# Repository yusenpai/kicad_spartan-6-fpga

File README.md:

# Spartan 6 FPGA Dev Board

Đây là thiết kế của một board FPGA dựa trên Xilinx Spartan-6 XC6SLX16, kiểu chân BGA 324 chân. Board tương thích với slot mini PCI Express. Trên board tích hợp 256MB DRAM DDR3, 1Gb NAND Flash và 32Mb NOR Flash phục vụ cho mục đích lưu trữ file cấu hình FPGA.
Board này phục vụ cho mục đích học tập, nghiên cứu liên quan tới FPGA.

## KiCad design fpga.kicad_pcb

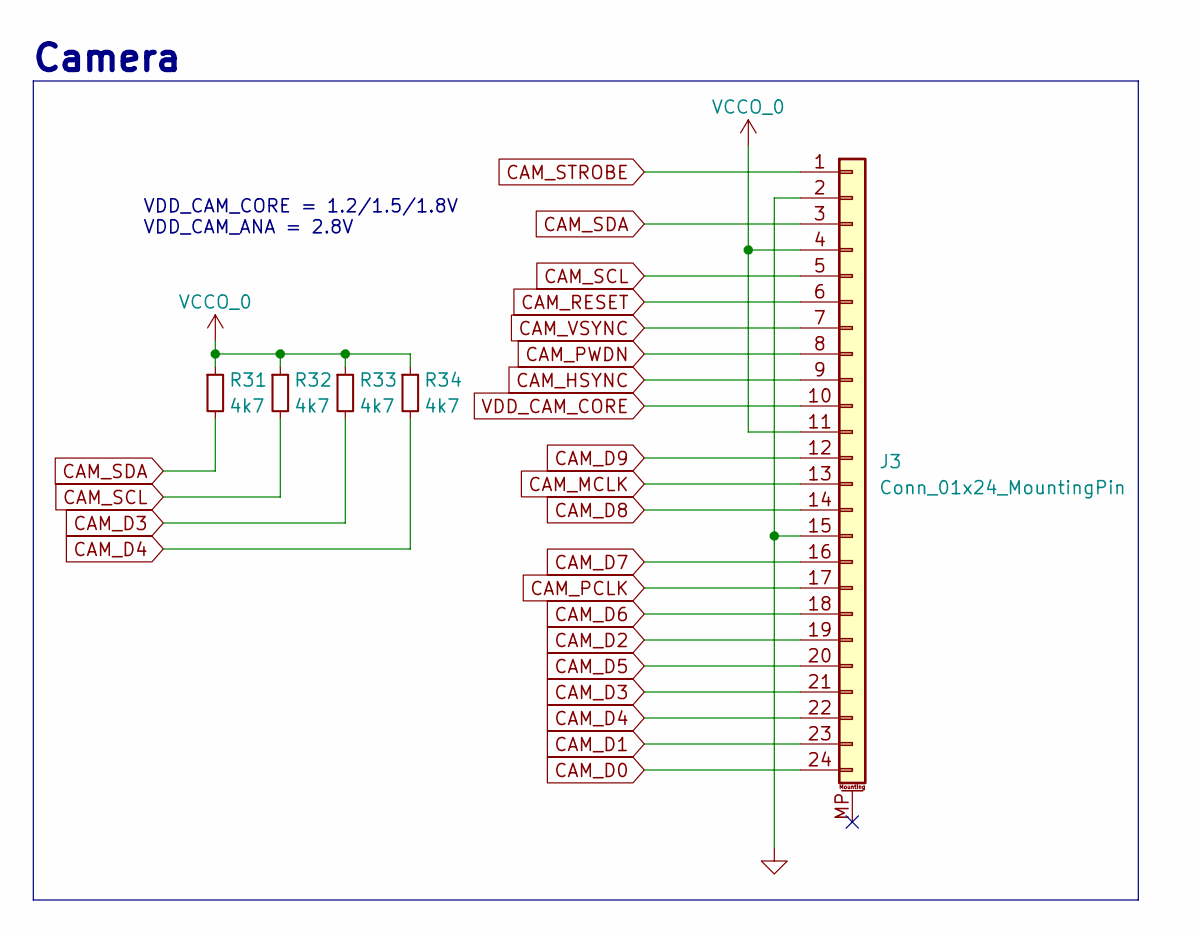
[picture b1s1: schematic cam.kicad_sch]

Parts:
J3: Conn_01x24_MountingPin; FPC-24P0.5
R31, R32, R33, R34: 4k7; R_0402_1005Metric

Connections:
+3V3: J3.4, J3.11, R31.1, R32.1, R33.1, R34.1; also elsewhere on the board
CAM_D0: J3.24; also elsewhere on the board
CAM_D1: J3.23; also elsewhere on the board
CAM_D2: J3.19; also elsewhere on the board
CAM_D3: J3.21, R33.2; also elsewhere on the board
CAM_D4: J3.22, R34.2; also elsewhere on the board
CAM_D5: J3.20; also elsewhere on the board
CAM_D6: J3.18; also elsewhere on the board
CAM_D7: J3.16; also elsewhere on the board
CAM_D8: J3.14; also elsewhere on the board
CAM_D9: J3.12; also elsewhere on the board
CAM_HSYNC: J3.9; also elsewhere on the board
CAM_MCLK: J3.13; also elsewhere on the board
CAM_PCLK: J3.17; also elsewhere on the board
CAM_PWDN: J3.8; also elsewhere on the board
CAM_RESET: J3.6; also elsewhere on the board
CAM_SCL: J3.5, R32.2; also elsewhere on the board
CAM_SDA: J3.3, R31.2; also elsewhere on the board
CAM_STROBE: J3.1; also elsewhere on the board
CAM_VSYNC: J3.7; also elsewhere on the board
GND: J3.2, J3.15; also elsewhere on the board
VDD_CAM_CORE: J3.10; also elsewhere on the board

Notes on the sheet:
Camera
VDD_CAM_CORE = 1.2/1.5/1.8V VDD_CAM_ANA = 2.8V

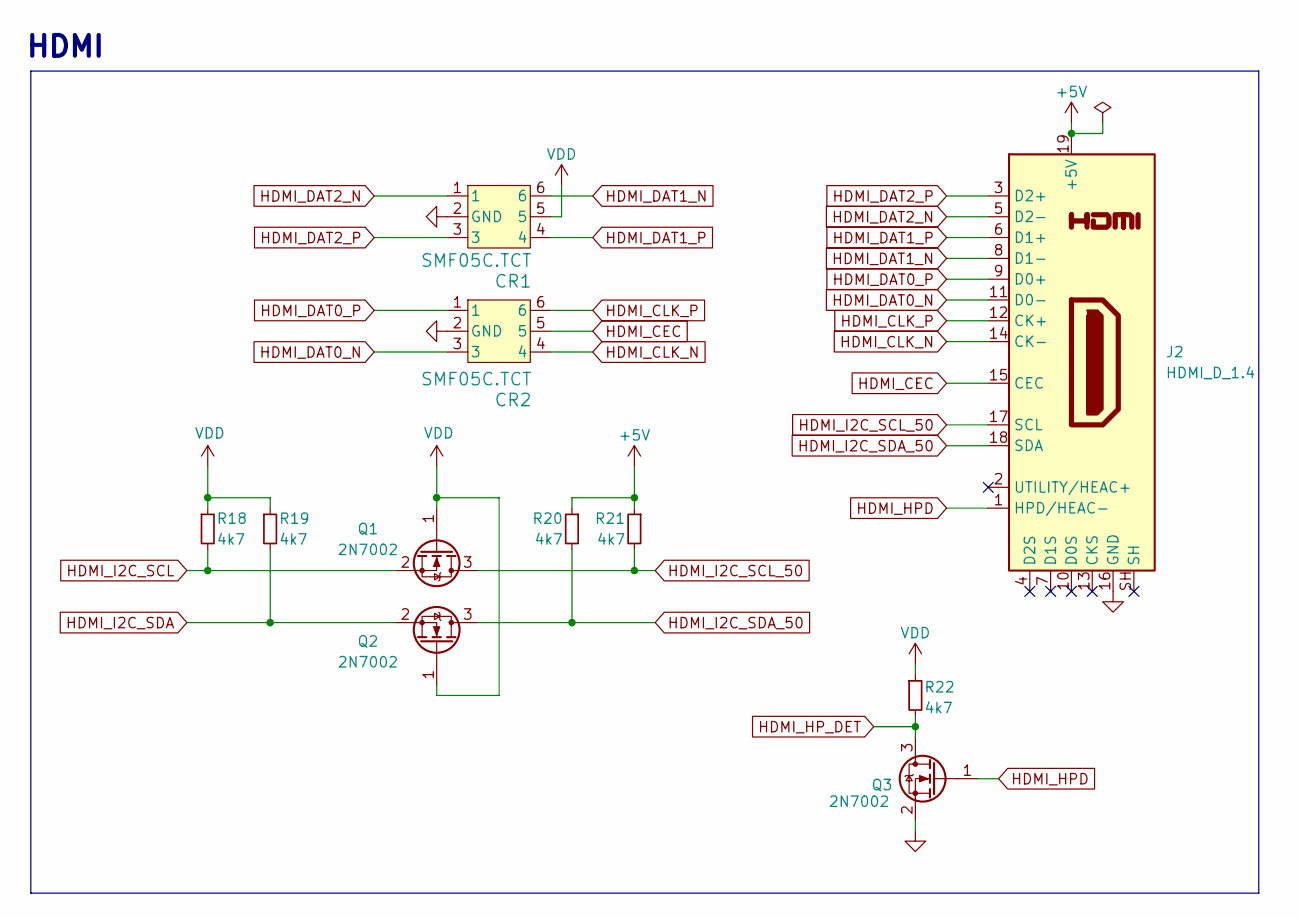
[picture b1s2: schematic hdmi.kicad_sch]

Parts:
CR1, CR2: SMF05C.TCT; TSOT-23-6
J2: HDMI_D_1.4; HDMI_Micro-D_Molex_46765-0x01
Q1, Q2, Q3: 2N7002; SOT-23
R18, R19, R20, R21, R22: 4k7; R_0402_1005Metric

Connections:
+3V3: CR1.5, Q1.1 (G), Q2.1 (G), R18.1, R19.1, R22.1; also elsewhere on the board
+5V: J2.19 (+5V), R20.1, R21.1; also elsewhere on the board
GND: CR1.2 (GND), CR2.2 (GND), J2.16 (GND), Q3.2 (S); also elsewhere on the board
HDMI_CEC: CR2.5, J2.15 (CEC); also elsewhere on the board
HDMI_CLK_N: CR2.4, J2.14 (CK-); also elsewhere on the board
HDMI_CLK_P: CR2.6, J2.12 (CK+); also elsewhere on the board
HDMI_DAT0_N: CR2.3, J2.11 (D0-); also elsewhere on the board
HDMI_DAT0_P: CR2.1, J2.9 (D0+); also elsewhere on the board
HDMI_DAT1_N: CR1.6, J2.8 (D1-); also elsewhere on the board
HDMI_DAT1_P: CR1.4, J2.6 (D1+); also elsewhere on the board
HDMI_DAT2_N: CR1.1, J2.5 (D2-); also elsewhere on the board
HDMI_DAT2_P: CR1.3, J2.3 (D2+); also elsewhere on the board
HDMI_HPD: J2.1 (HPD/HEAC-), Q3.1 (G)
HDMI_HP_DET: Q3.3 (D), R22.2; also elsewhere on the board
HDMI_I2C_SCL: Q1.2 (S), R18.2; also elsewhere on the board
HDMI_I2C_SCL_50: J2.17 (SCL), Q1.3 (D), R21.2
HDMI_I2C_SDA: Q2.2 (S), R19.2; also elsewhere on the board
HDMI_I2C_SDA_50: J2.18 (SDA), Q2.3 (D), R20.2

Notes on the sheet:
HDMI

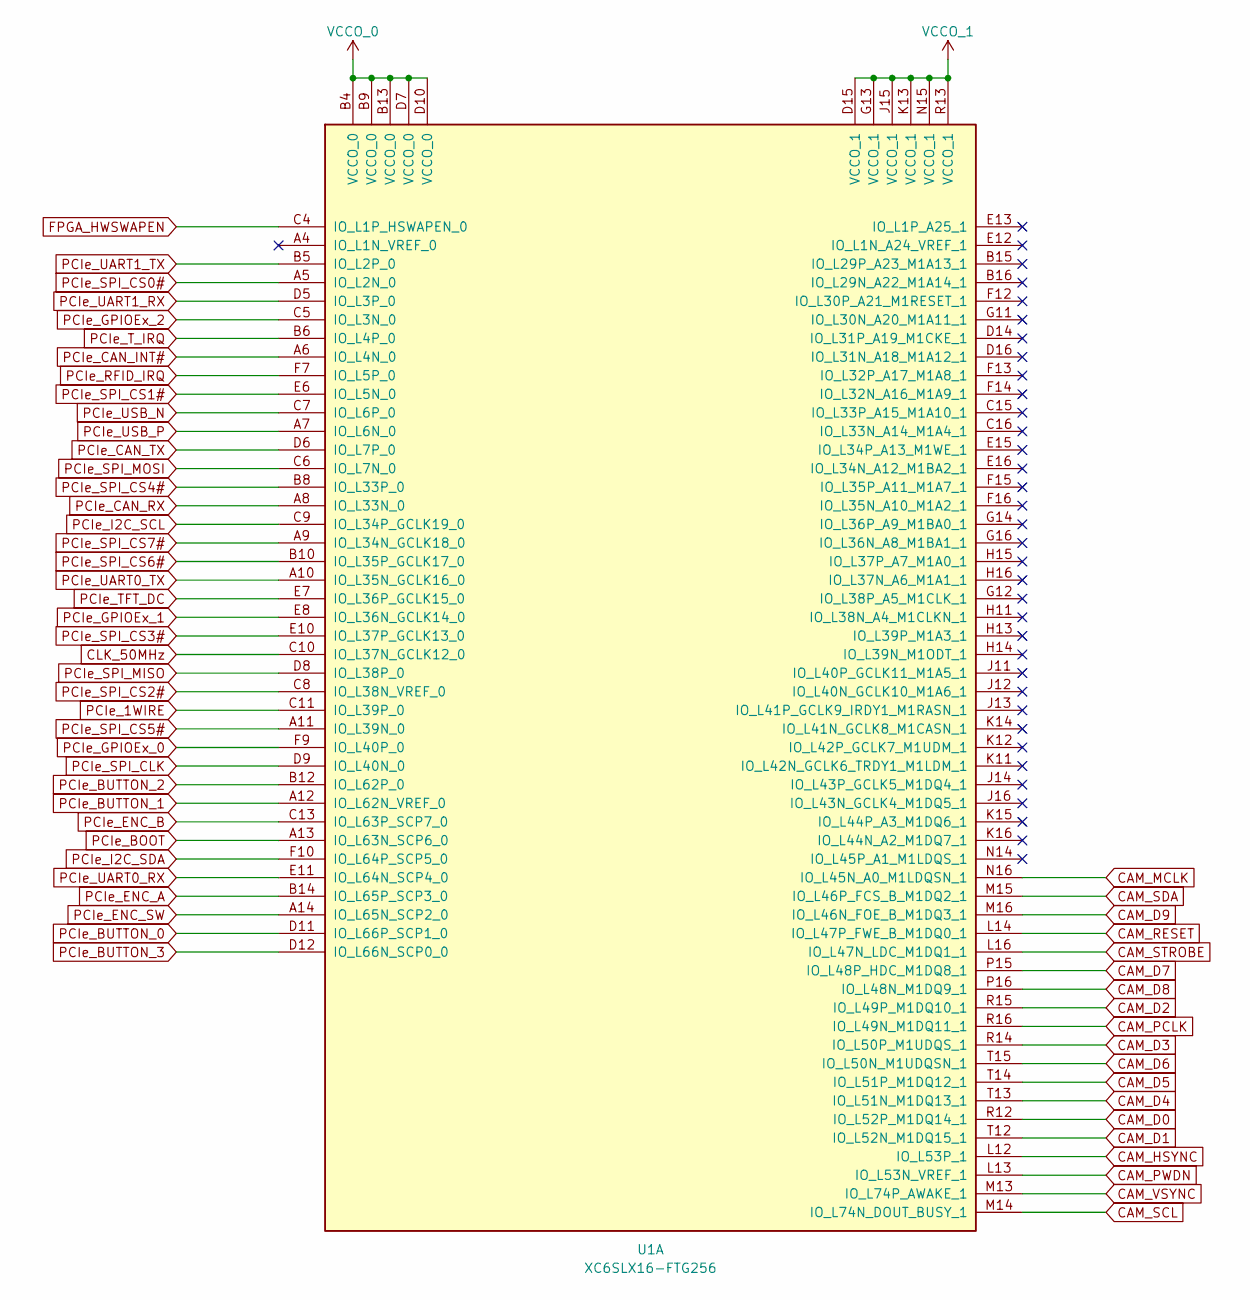
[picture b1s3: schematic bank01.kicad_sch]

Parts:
U1: XC6SLX16-FTG256; BGA-256_17.0x17.0mm_Layout16x16_P1.0mm_Ball0.5mm_Pad0.4mm_N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

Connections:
+2V8: U1.D15 (VCCO_1), U1.G13 (VCCO_1), U1.J15 (VCCO_1), U1.K13 (VCCO_1), U1.N15 (VCCO_1), U1.R13 (VCCO_1); also elsewhere on the board
+3V3: U1.B4 (VCCO_0), U1.B9 (VCCO_0), U1.B13 (VCCO_0), U1.D7 (VCCO_0), U1.D10 (VCCO_0); also elsewhere on the board
CAM_D0: U1.R12 (IO_L52P_M1DQ14_1); also elsewhere on the board
CAM_D1: U1.T12 (IO_L52N_M1DQ15_1); also elsewhere on the board
CAM_D2: U1.R15 (IO_L49P_M1DQ10_1); also elsewhere on the board
CAM_D3: U1.R14 (IO_L50P_M1UDQS_1); also elsewhere on the board
CAM_D4: U1.T13 (IO_L51N_M1DQ13_1); also elsewhere on the board
CAM_D5: U1.T14 (IO_L51P_M1DQ12_1); also elsewhere on the board
CAM_D6: U1.T15 (IO_L50N_M1UDQSN_1); also elsewhere on the board
CAM_D7: U1.P15 (IO_L48P_HDC_M1DQ8_1); also elsewhere on the board
CAM_D8: U1.P16 (IO_L48N_M1DQ9_1); also elsewhere on the board
CAM_D9: U1.M16 (IO_L46N_FOE_B_M1DQ3_1); also elsewhere on the board
CAM_HSYNC: U1.L12 (IO_L53P_1); also elsewhere on the board
CAM_MCLK: U1.N16 (IO_L45N_A0_M1LDQSN_1); also elsewhere on the board
CAM_PCLK: U1.R16 (IO_L49N_M1DQ11_1); also elsewhere on the board
CAM_PWDN: U1.L13 (IO_L53N_VREF_1); also elsewhere on the board
CAM_RESET: U1.L14 (IO_L47P_FWE_B_M1DQ0_1); also elsewhere on the board
CAM_SCL: U1.M14 (IO_L74N_DOUT_BUSY_1); also elsewhere on the board
CAM_SDA: U1.M15 (IO_L46P_FCS_B_M1DQ2_1); also elsewhere on the board
CAM_STROBE: U1.L16 (IO_L47N_LDC_M1DQ1_1); also elsewhere on the board
CAM_VSYNC: U1.M13 (IO_L74P_AWAKE_1); also elsewhere on the board
CLK_50MHz: U1.C10 (IO_L37N_GCLK12_0); also elsewhere on the board
FPGA_HWSWAPEN: U1.C4 (IO_L1P_HSWAPEN_0); also elsewhere on the board
PCIe_1WIRE: U1.C11 (IO_L39P_0); also elsewhere on the board
PCIe_BOOT: U1.A13 (IO_L63N_SCP6_0); also elsewhere on the board
PCIe_BUTTON_0: U1.D11 (IO_L66P_SCP1_0); also elsewhere on the board
PCIe_BUTTON_1: U1.A12 (IO_L62N_VREF_0); also elsewhere on the board
PCIe_BUTTON_2: U1.B12 (IO_L62P_0); also elsewhere on the board
PCIe_BUTTON_3: U1.D12 (IO_L66N_SCP0_0); also elsewhere on the board
PCIe_CAN_INT#: U1.A6 (IO_L4N_0); also elsewhere on the board
PCIe_CAN_RX: U1.A8 (IO_L33N_0); also elsewhere on the board
PCIe_CAN_TX: U1.D6 (IO_L7P_0); also elsewhere on the board
PCIe_ENC_A: U1.B14 (IO_L65P_SCP3_0); also elsewhere on the board
PCIe_ENC_B: U1.C13 (IO_L63P_SCP7_0); also elsewhere on the board
PCIe_ENC_SW: U1.A14 (IO_L65N_SCP2_0); also elsewhere on the board
PCIe_GPIOEx_0: U1.F9 (IO_L40P_0); also elsewhere on the board
PCIe_GPIOEx_1: U1.E8 (IO_L36N_GCLK14_0); also elsewhere on the board
PCIe_GPIOEx_2: U1.C5 (IO_L3N_0); also elsewhere on the board
PCIe_I2C_SCL: U1.C9 (IO_L34P_GCLK19_0); also elsewhere on the board
PCIe_I2C_SDA: U1.F10 (IO_L64P_SCP5_0); also elsewhere on the board
PCIe_RFID_IRQ: U1.F7 (IO_L5P_0); also elsewhere on the board
PCIe_SPI_CLK: U1.D9 (IO_L40N_0); also elsewhere on the board
PCIe_SPI_CS0#: U1.A5 (IO_L2N_0); also elsewhere on the board
PCIe_SPI_CS1#: U1.E6 (IO_L5N_0); also elsewhere on the board
PCIe_SPI_CS2#: U1.C8 (IO_L38N_VREF_0); also elsewhere on the board
PCIe_SPI_CS3#: U1.E10 (IO_L37P_GCLK13_0); also elsewhere on the board
PCIe_SPI_CS4#: U1.B8 (IO_L33P_0); also elsewhere on the board
PCIe_SPI_CS5#: U1.A11 (IO_L39N_0); also elsewhere on the board
PCIe_SPI_CS6#: U1.B10 (IO_L35P_GCLK17_0); also elsewhere on the board
PCIe_SPI_CS7#: U1.A9 (IO_L34N_GCLK18_0); also elsewhere on the board
PCIe_SPI_MISO: U1.D8 (IO_L38P_0); also elsewhere on the board
PCIe_SPI_MOSI: U1.C6 (IO_L7N_0); also elsewhere on the board
PCIe_TFT_DC: U1.E7 (IO_L36P_GCLK15_0); also elsewhere on the board
PCIe_T_IRQ: U1.B6 (IO_L4P_0); also elsewhere on the board
PCIe_UART0_RX: U1.E11 (IO_L64N_SCP4_0); also elsewhere on the board
PCIe_UART0_TX: U1.A10 (IO_L35N_GCLK16_0); also elsewhere on the board
PCIe_UART1_RX: U1.D5 (IO_L3P_0); also elsewhere on the board
PCIe_UART1_TX: U1.B5 (IO_L2P_0); also elsewhere on the board
PCIe_USB_N: U1.C7 (IO_L6P_0); also elsewhere on the board
PCIe_USB_P: U1.A7 (IO_L6N_0); also elsewhere on the board

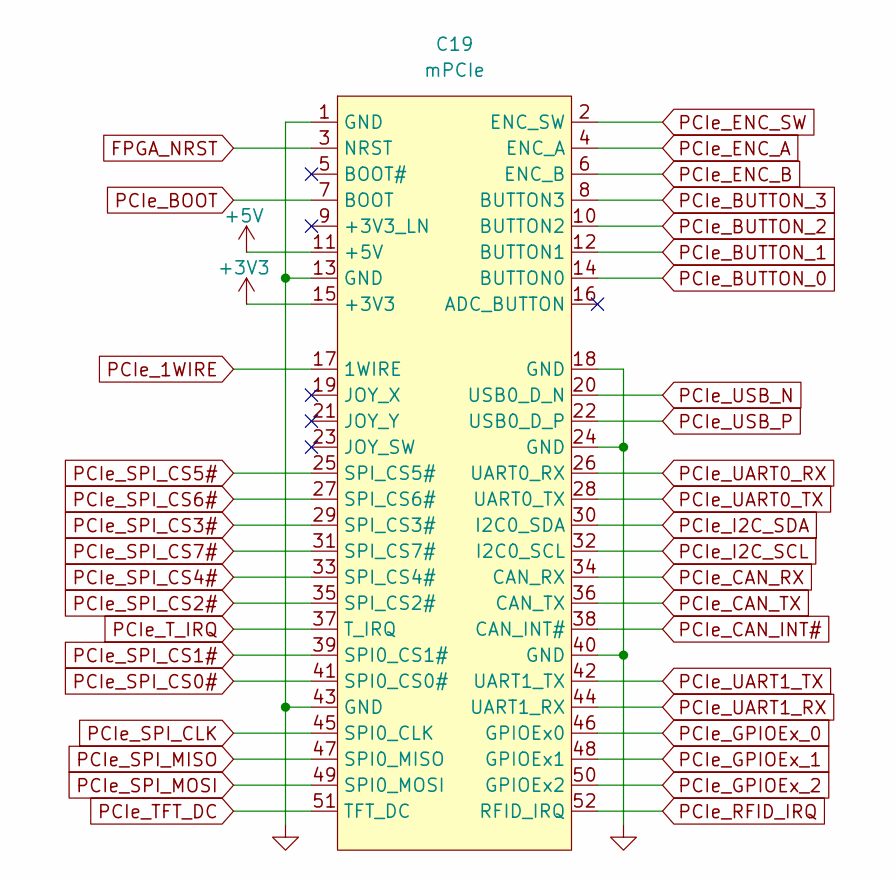
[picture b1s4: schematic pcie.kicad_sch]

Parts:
C19: mPCIe; mpcie-full-card

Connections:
+3V3: C19.15 (+3V3); also elsewhere on the board
+5V: C19.11 (+5V); also elsewhere on the board
FPGA_NRST: C19.3 (NRST); also elsewhere on the board
GND: C19.1 (GND), C19.13 (GND), C19.18 (GND), C19.24 (GND), C19.40 (GND), C19.43 (GND); also elsewhere on the board
PCIe_1WIRE: C19.17 (1WIRE); also elsewhere on the board
PCIe_BOOT: C19.7 (BOOT); also elsewhere on the board
PCIe_BUTTON_0: C19.14 (BUTTON0); also elsewhere on the board
PCIe_BUTTON_1: C19.12 (BUTTON1); also elsewhere on the board
PCIe_BUTTON_2: C19.10 (BUTTON2); also elsewhere on the board
PCIe_BUTTON_3: C19.8 (BUTTON3); also elsewhere on the board
PCIe_CAN_INT#: C19.38 (CAN_INT#); also elsewhere on the board
PCIe_CAN_RX: C19.34 (CAN_RX); also elsewhere on the board
PCIe_CAN_TX: C19.36 (CAN_TX); also elsewhere on the board
PCIe_ENC_A: C19.4 (ENC_A); also elsewhere on the board
PCIe_ENC_B: C19.6 (ENC_B); also elsewhere on the board
PCIe_ENC_SW: C19.2 (ENC_SW); also elsewhere on the board
PCIe_GPIOEx_0: C19.46 (GPIOEx0); also elsewhere on the board
PCIe_GPIOEx_1: C19.48 (GPIOEx1); also elsewhere on the board
PCIe_GPIOEx_2: C19.50 (GPIOEx2); also elsewhere on the board
PCIe_I2C_SCL: C19.32 (I2C0_SCL); also elsewhere on the board
PCIe_I2C_SDA: C19.30 (I2C0_SDA); also elsewhere on the board
PCIe_RFID_IRQ: C19.52 (RFID_IRQ); also elsewhere on the board
PCIe_SPI_CLK: C19.45 (SPI0_CLK); also elsewhere on the board
PCIe_SPI_CS0#: C19.41 (SPI0_CS0#); also elsewhere on the board
PCIe_SPI_CS1#: C19.39 (SPI0_CS1#); also elsewhere on the board
PCIe_SPI_CS2#: C19.35 (SPI_CS2#); also elsewhere on the board
PCIe_SPI_CS3#: C19.29 (SPI_CS3#); also elsewhere on the board
PCIe_SPI_CS4#: C19.33 (SPI_CS4#); also elsewhere on the board
PCIe_SPI_CS5#: C19.25 (SPI_CS5#); also elsewhere on the board
PCIe_SPI_CS6#: C19.27 (SPI_CS6#); also elsewhere on the board
PCIe_SPI_CS7#: C19.31 (SPI_CS7#); also elsewhere on the board
PCIe_SPI_MISO: C19.47 (SPI0_MISO); also elsewhere on the board
PCIe_SPI_MOSI: C19.49 (SPI0_MOSI); also elsewhere on the board
PCIe_TFT_DC: C19.51 (TFT_DC); also elsewhere on the board
PCIe_T_IRQ: C19.37 (T_IRQ); also elsewhere on the board
PCIe_UART0_RX: C19.26 (UART0_RX); also elsewhere on the board
PCIe_UART0_TX: C19.28 (UART0_TX); also elsewhere on the board
PCIe_UART1_RX: C19.44 (UART1_RX); also elsewhere on the board
PCIe_UART1_TX: C19.42 (UART1_TX); also elsewhere on the board
PCIe_USB_N: C19.20 (USB0_D_N); also elsewhere on the board
PCIe_USB_P: C19.22 (USB0_D_P); also elsewhere on the board

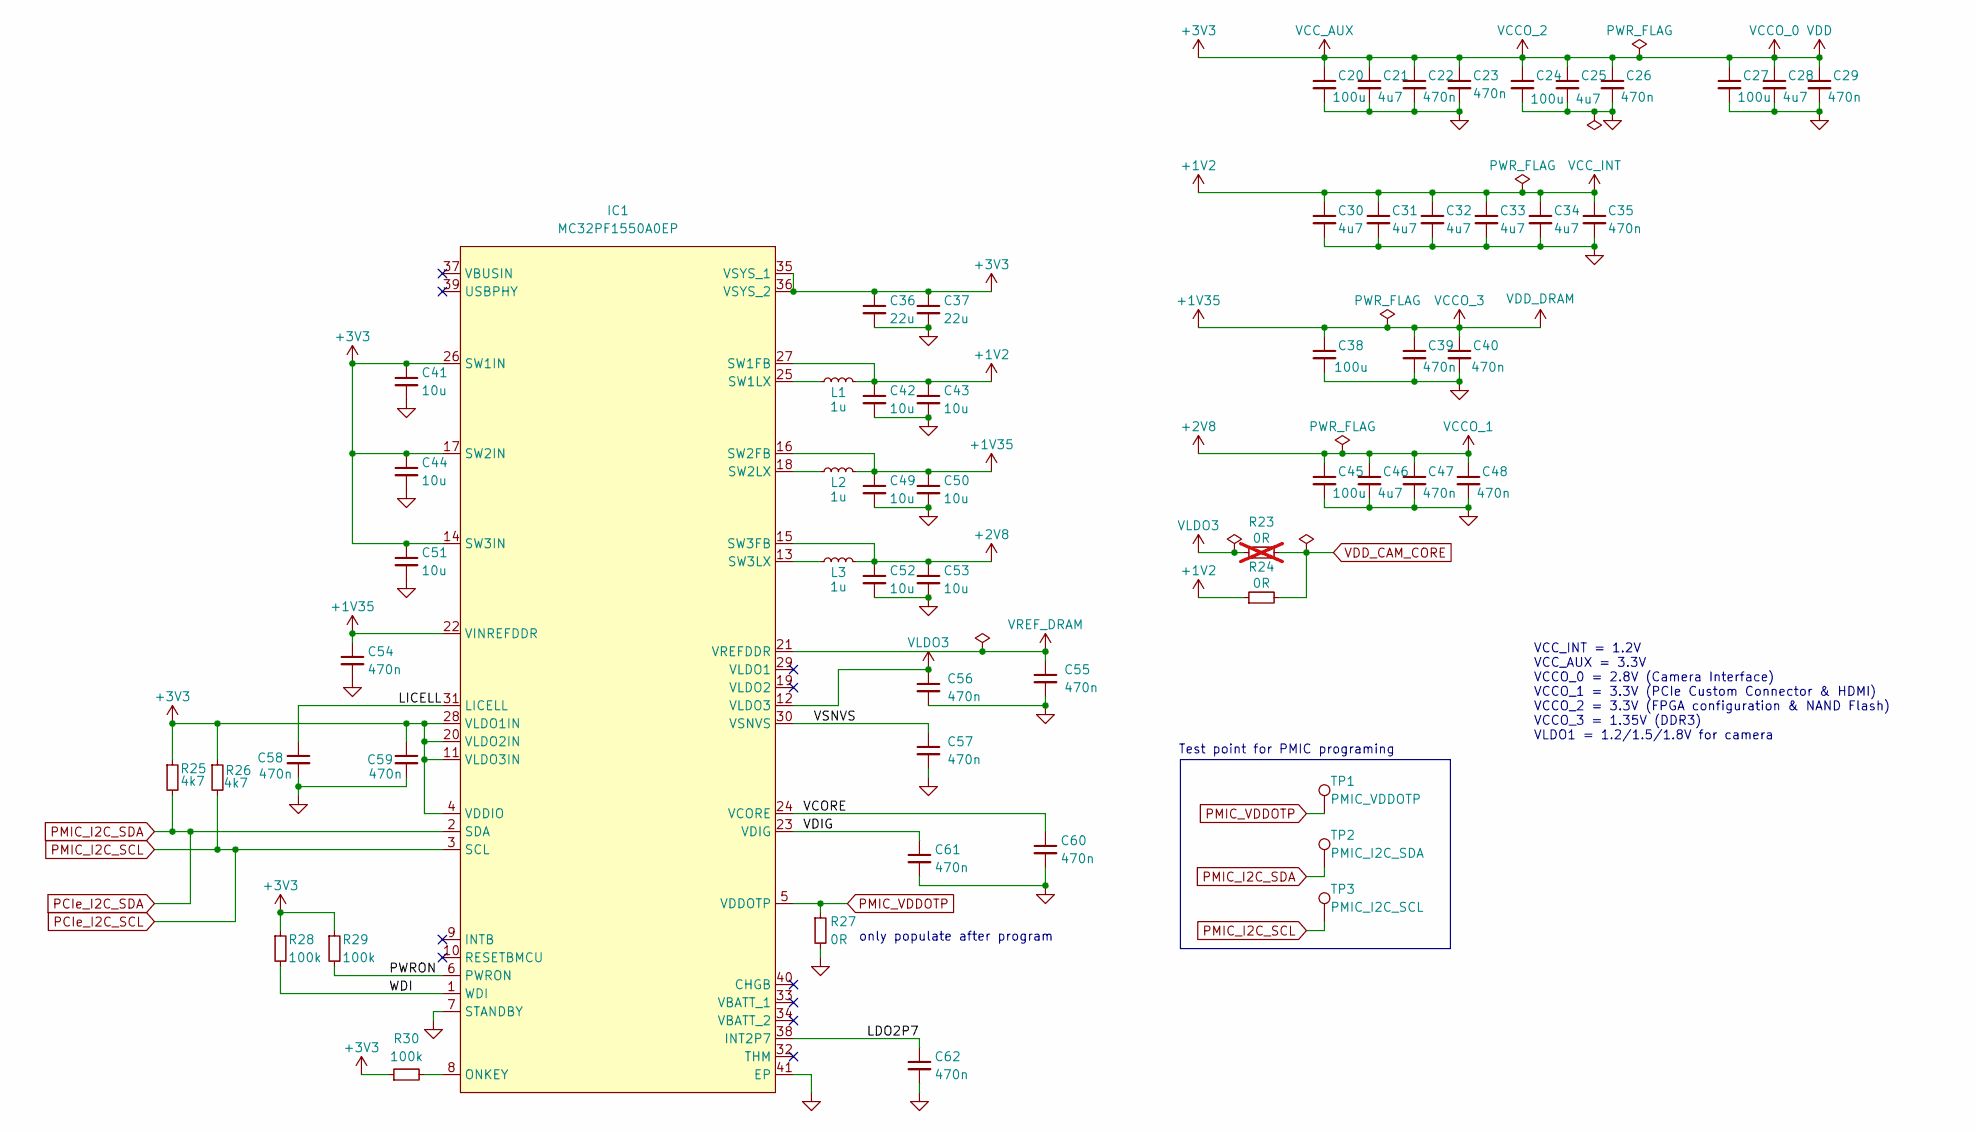
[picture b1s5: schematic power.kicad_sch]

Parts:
C20, C24, C27, C38, C45: 100u; C_1206_3216Metric
C21, C25, C28, C30, C31, C32, C33, C34, C46: 4u7; C_0603_1608Metric
C22, C23, C26, C29, C35, C39, C40, C47, C48, C54, C55, C56, C57, C58, C59, C60, C61, C62: 470n; C_0402_1005Metric
C36, C37: 22u; C_0603_1608Metric
C41, C42, C43, C44, C49, C50, C51, C52, C53: 10u; C_0603_1608Metric
IC1: MC32PF1550A0EP; QFN-40-1EP_5x5mm_P0.4mm_EP3.8x3.8mm; Manufacturer_Part_Number MC32PF1550A0EP; Mouser Part Number 771-MC32PF1550A0EP
L1, L2, L3: 1u; L_Wurth_WE-LQSH-4020
R23: 0R; R_0402_1005Metric; not fitted
R24, R27: 0R; R_0402_1005Metric
R25, R26: 4k7; R_0402_1005Metric
R28, R29, R30: 100k; R_0402_1005Metric
TP1: PMIC_VDDOTP; TestPoint_Pad_D1.0mm
TP2: PMIC_I2C_SDA; TestPoint_Pad_D1.0mm
TP3: PMIC_I2C_SCL; TestPoint_Pad_D1.0mm

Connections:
+1V2: C30.1, C31.1, C32.1, C33.1, C34.1, C35.1, C42.1, C43.1, IC1.27 (SW1FB), L1.2, R24.1; also elsewhere on the board
+1V35: C38.1, C39.1, C40.1, C49.1, C50.1, C54.1, IC1.16 (SW2FB), IC1.22 (VINREFDDR), L2.2; also elsewhere on the board
+2V8: C45.1, C46.1, C47.1, C48.1, C52.1, C53.1, IC1.15 (SW3FB), L3.2; also elsewhere on the board
+3V3: C20.1, C21.1, C22.1, C23.1, C24.1, C25.1, C26.1, C27.1, C28.1, C29.1, C36.1, C37.1, C41.1, C44.1, C51.1, C59.1, IC1.4 (VDDIO), IC1.11 (VLDO3IN), IC1.14 (SW3IN), IC1.17 (SW2IN), IC1.20 (VLDO2IN), IC1.26 (SW1IN), IC1.28 (VLDO1IN), IC1.35 (VSYS_1), IC1.36 (VSYS_2), R25.1, R26.1, R28.1, R29.1, R30.1; also elsewhere on the board
/Power/LDO2P7: C62.1, IC1.38 (INT2P7)
/Power/LICELL: C58.1, IC1.31 (LICELL)
/Power/PWRON: IC1.6 (PWRON), R29.2
/Power/VCORE: C60.1, IC1.24 (VCORE)
/Power/VDIG: C61.1, IC1.23 (VDIG)
/Power/VSNVS: C57.1, IC1.30 (VSNVS)
/Power/WDI: IC1.1 (WDI), R28.2
GND: C20.2, C21.2, C22.2, C23.2, C24.2, C25.2, C26.2, C27.2, C28.2, C29.2, C30.2, C31.2, C32.2, C33.2, C34.2, C35.2, C36.2, C37.2, C38.2, C39.2, C40.2, C41.2, C42.2, C43.2, C44.2, C45.2, C46.2, C47.2, C48.2, C49.2, C50.2, C51.2, C52.2, C53.2, C54.2, C55.2, C56.2, C57.2, C58.2, C59.2, C60.2, C61.2, C62.2, IC1.7 (STANDBY), IC1.41 (EP), R27.2; also elsewhere on the board
unnamed: IC1.8 (ONKEY), R30.2
unnamed: IC1.25 (SW1LX), L1.1
unnamed: IC1.18 (SW2LX), L2.1
unnamed: IC1.13 (SW3LX), L3.1
PCIe_I2C_SCL: IC1.3 (SCL), R26.2, TP3.1; also elsewhere on the board
PCIe_I2C_SDA: IC1.2 (SDA), R25.2, TP2.1; also elsewhere on the board
PMIC_VDDOTP: IC1.5 (VDDOTP), R27.1, TP1.1
VDD_CAM_CORE: R23.2, R24.2; also elsewhere on the board
VLDO3: C56.1, IC1.12 (VLDO3), R23.1
VREF_DRAM: C55.1, IC1.21 (VREFDDR); also elsewhere on the board

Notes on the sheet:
only populate after program
VCC_INT = 1.2V VCC_AUX = 3.3V VCCO_0 = 2.8V (Camera Interface) VCCO_1 = 3.3V (PCIe Custom Connector & HDMI) VCCO_2 = 3.3V (FPGA configuration & NAND Flash) VCCO_3 = 1.35V (DDR3) VLDO1 = 1.2/1.5/1.8V for camera
Test point for PMIC programing

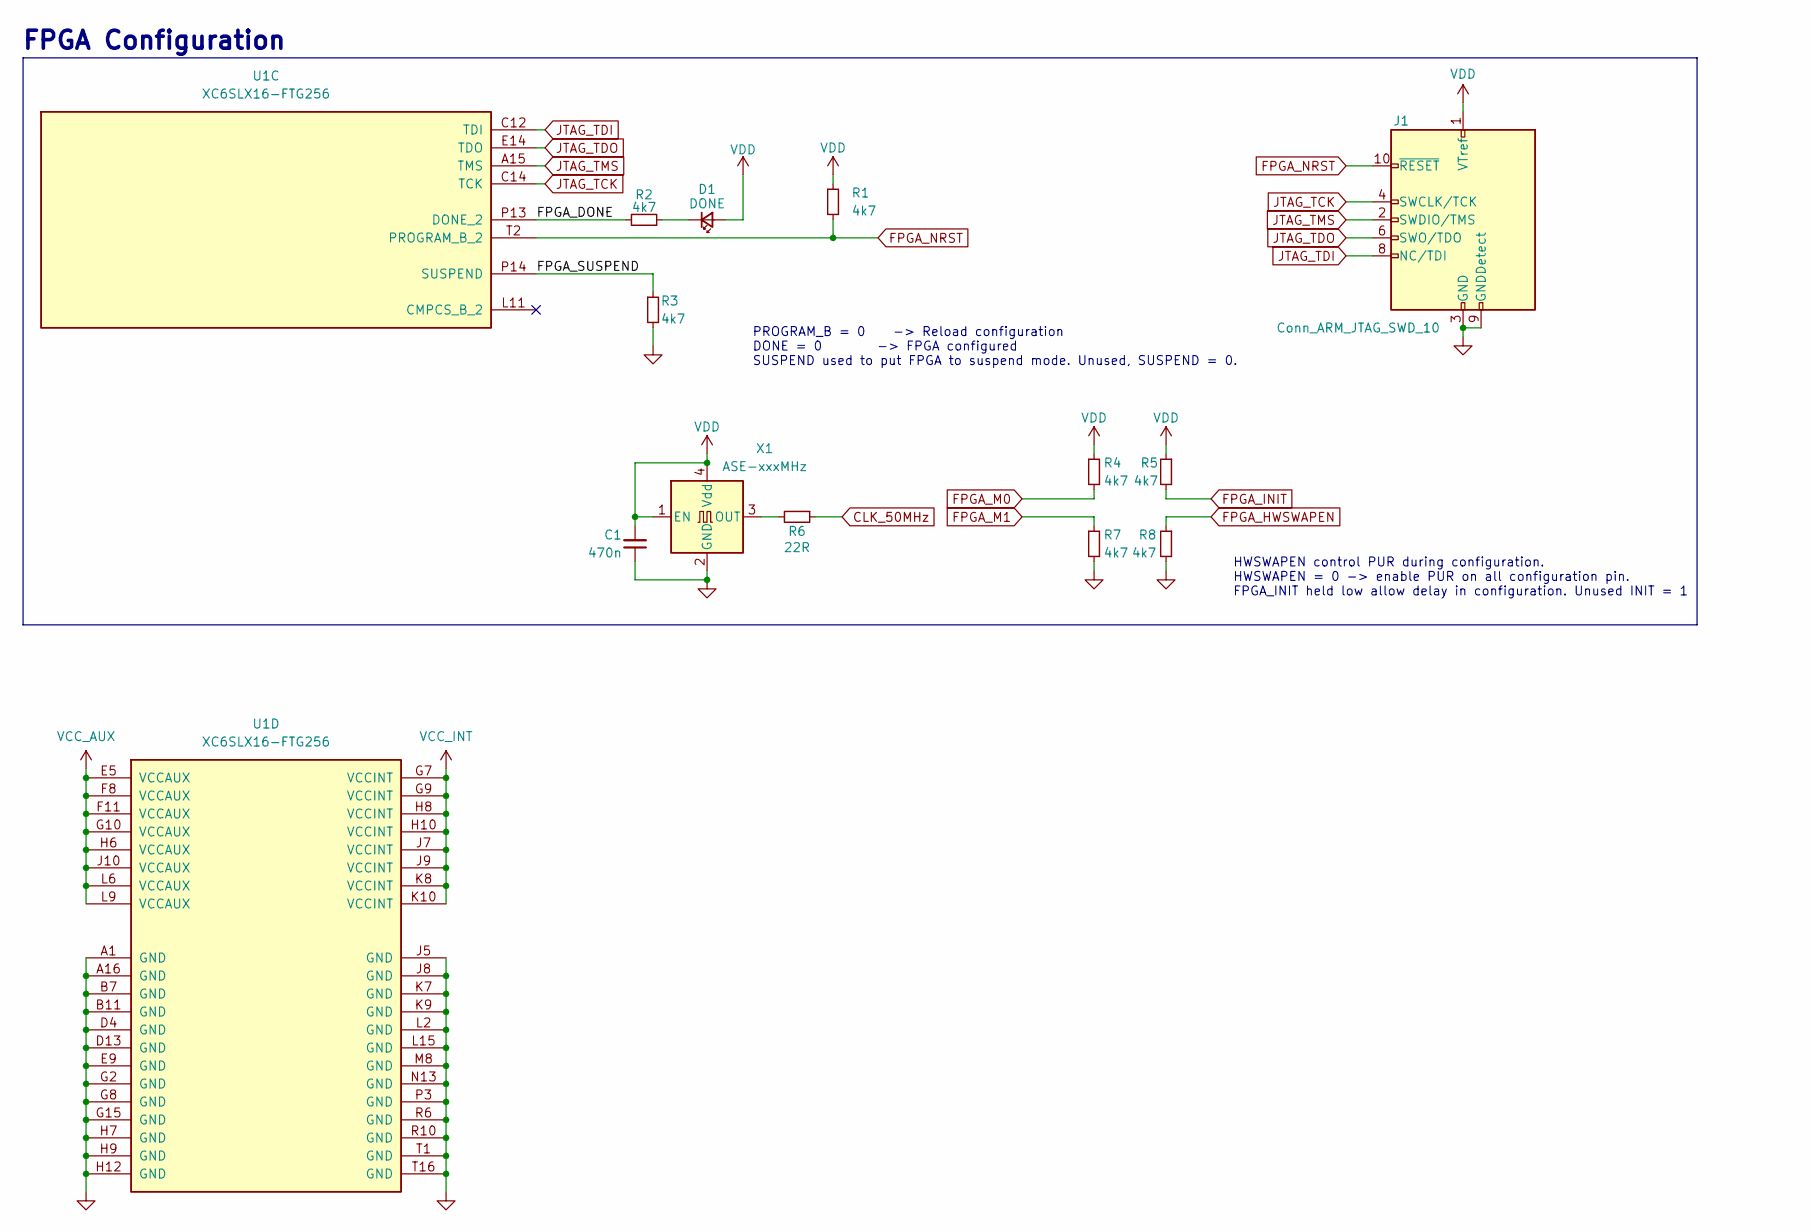
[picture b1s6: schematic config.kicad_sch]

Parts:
C1: 470n; C_0402_1005Metric
D1: DONE; LED_0603_1608Metric
J1: Conn_ARM_JTAG_SWD_10; PinHeader_2x05_P1.27mm_Vertical_SMD
R1, R2, R3, R4, R5, R7, R8: 4k7; R_0402_1005Metric
R6: 22R; R_0402_1005Metric
U1: XC6SLX16-FTG256; BGA-256_17.0x17.0mm_Layout16x16_P1.0mm_Ball0.5mm_Pad0.4mm_N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
X1: ASE-xxxMHz; Oscillator_SMD_Abracon_ASE-4Pin_3.2x2.5mm

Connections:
+1V2: U1.G7 (VCCINT), U1.G9 (VCCINT), U1.H8 (VCCINT), U1.H10 (VCCINT), U1.J7 (VCCINT), U1.J9 (VCCINT), U1.K8 (VCCINT), U1.K10 (VCCINT); also elsewhere on the board
+3V3: C1.2, D1.2 (A), J1.1 (VTref), R1.1, R4.1, R5.1, U1.E5 (VCCAUX), U1.F8 (VCCAUX), U1.F11 (VCCAUX), U1.G10 (VCCAUX), U1.H6 (VCCAUX), U1.J10 (VCCAUX), U1.L6 (VCCAUX), U1.L9 (VCCAUX), X1.1 (EN), X1.4 (Vdd); also elsewhere on the board
/FPGA Configuration/FPGA_DONE: R2.2, U1.P13 (DONE_2)
/FPGA Configuration/FPGA_SUSPEND: R3.1, U1.P14 (SUSPEND)
CLK_50MHz: R6.1; also elsewhere on the board
FPGA_HWSWAPEN: R8.1; also elsewhere on the board
FPGA_INIT: R5.2; also elsewhere on the board
FPGA_M0: R4.2; also elsewhere on the board
FPGA_M1: R7.1; also elsewhere on the board
FPGA_NRST: J1.10 (~RESET), R1.2, U1.T2 (PROGRAM_B_2); also elsewhere on the board
GND: C1.1, J1.3 (GND), J1.5 (GND), J1.9 (GNDDetect), R3.2, R7.2, R8.2, U1.A1 (GND), U1.A16 (GND), U1.B7 (GND), U1.B11 (GND), U1.D4 (GND), U1.D13 (GND), U1.E9 (GND), U1.G2 (GND), U1.G8 (GND), U1.G15 (GND), U1.H7 (GND), U1.H9 (GND), U1.H12 (GND), U1.J5 (GND), U1.J8 (GND), U1.K7 (GND), U1.K9 (GND), U1.L2 (GND), U1.L15 (GND), U1.M8 (GND), U1.N13 (GND), U1.P3 (GND), U1.R6 (GND), U1.R10 (GND), U1.T1 (GND), U1.T16 (GND), X1.2 (GND); also elsewhere on the board
JTAG_TCK: J1.4 (SWCLK/TCK), U1.C14 (TCK)
JTAG_TDI: J1.8 (NC/TDI), U1.C12 (TDI)
JTAG_TDO: J1.6 (SWO/TDO), U1.E14 (TDO)
JTAG_TMS: J1.2 (SWDIO/TMS), U1.A15 (TMS)
unnamed: D1.1 (K), R2.1
unnamed: R6.2, X1.3 (OUT)

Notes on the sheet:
FPGA Configuration
PROGRAM_B = 0 -> Reload configuration DONE = 0 -> FPGA configured SUSPEND used to put FPGA to suspend mode. Unused, SUSPEND = 0.
HWSWAPEN control PUR during configuration. HWSWAPEN = 0 -> enable PUR on all configuration pin. FPGA_INIT held low allow delay in configuration. Unused INIT = 1

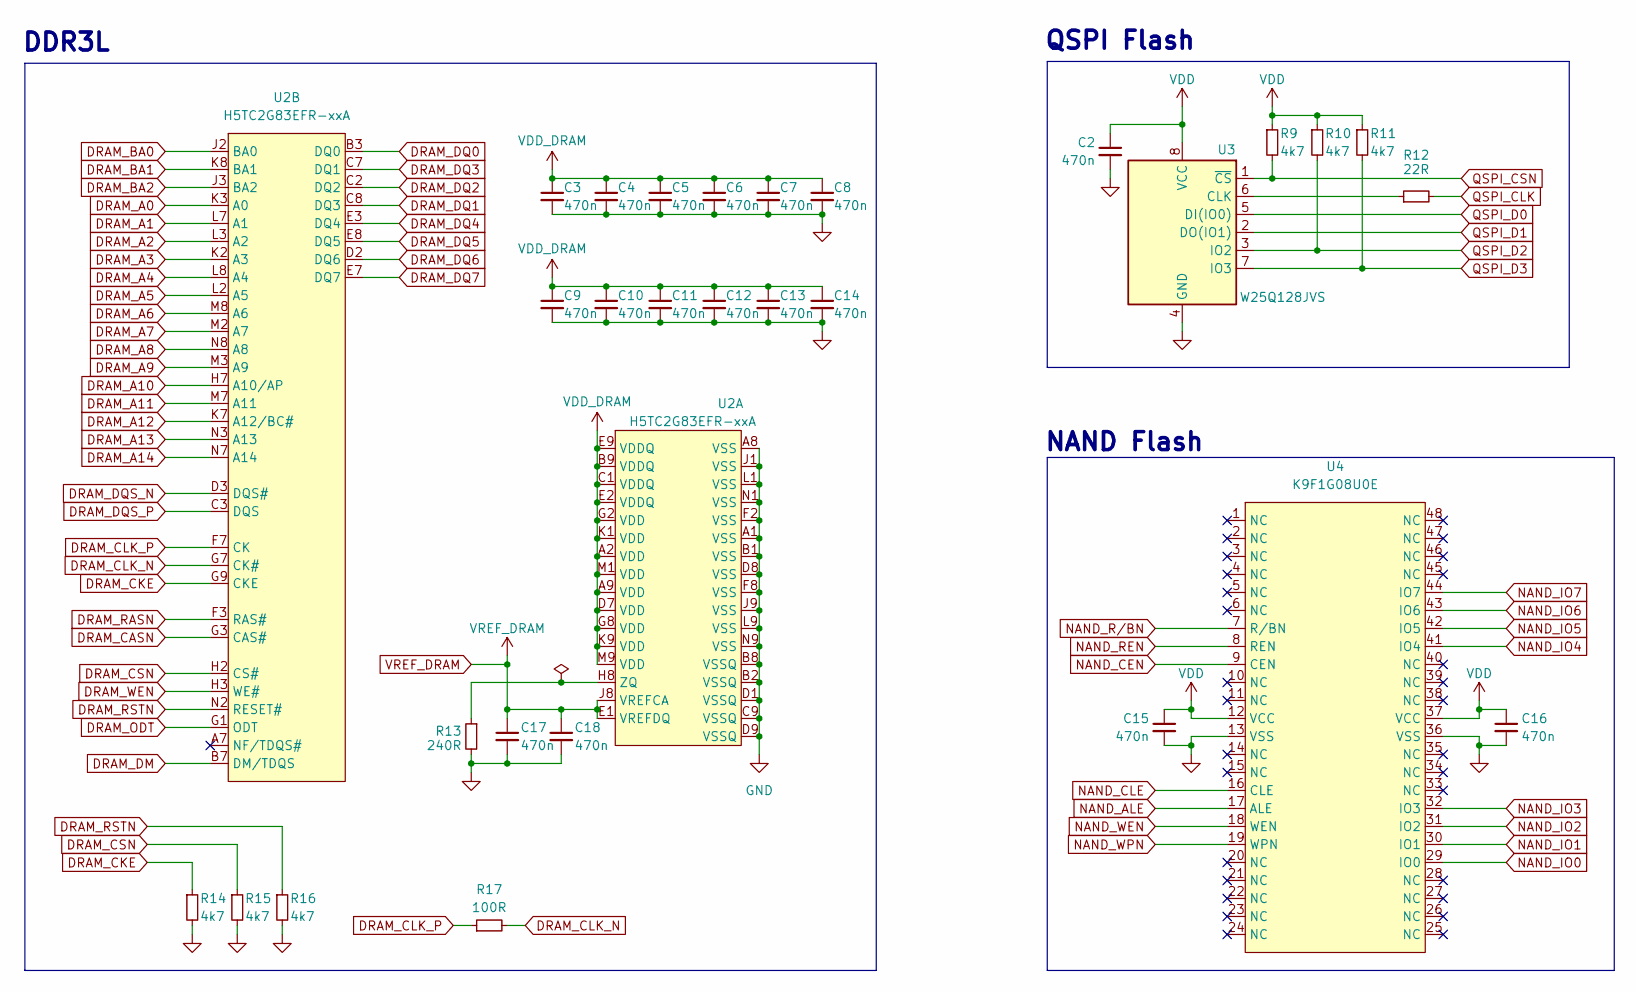
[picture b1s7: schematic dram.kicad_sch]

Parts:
C2, C3, C4, C5, C6, C7, C8, C9, C10, C11, C12, C13, C14, C15, C16, C17, C18: 470n; C_0402_1005Metric
R9, R10, R11, R14, R15, R16: 4k7; R_0402_1005Metric
R12: 22R; R_0402_1005Metric
R13: 240R; R_0402_1005Metric
R17: 100R; R_0402_1005Metric
U2: H5TC2G83EFR-xxA; FBGA-78_7.5x11mm_Layout2x3x13_P0.8mm
U3: W25Q128JVS; SOIC-8_5.23x5.23mm_P1.27mm
U4: K9F1G08U0E; TSOP-I-48_18.4x12mm_P0.5mm

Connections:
+1V35: C3.1, C4.1, C5.1, C6.1, C7.1, C8.1, C9.1, C10.1, C11.1, C12.1, C13.1, C14.1, U2.A2 (VDD), U2.A9 (VDD), U2.B9 (VDDQ), U2.C1 (VDDQ), U2.D7 (VDD), U2.E2 (VDDQ), U2.E9 (VDDQ), U2.G2 (VDD), U2.G8 (VDD), U2.K1 (VDD), U2.K9 (VDD), U2.M1 (VDD), U2.M9 (VDD); also elsewhere on the board
+3V3: C2.1, C15.1, C16.1, R9.1, R10.1, R11.1, U3.8 (VCC), U4.12 (VCC), U4.37 (VCC); also elsewhere on the board
DRAM_A0: U2.K3 (A0); also elsewhere on the board
DRAM_A1: U2.L7 (A1); also elsewhere on the board
DRAM_A2: U2.L3 (A2); also elsewhere on the board
DRAM_A3: U2.K2 (A3); also elsewhere on the board
DRAM_A4: U2.L8 (A4); also elsewhere on the board
DRAM_A5: U2.L2 (A5); also elsewhere on the board
DRAM_A6: U2.M8 (A6); also elsewhere on the board
DRAM_A7: U2.M2 (A7); also elsewhere on the board
DRAM_A8: U2.N8 (A8); also elsewhere on the board
DRAM_A9: U2.M3 (A9); also elsewhere on the board
DRAM_A10: U2.H7 (A10/AP); also elsewhere on the board
DRAM_A11: U2.M7 (A11); also elsewhere on the board
DRAM_A12: U2.K7 (A12/BC#); also elsewhere on the board
DRAM_A13: U2.N3 (A13); also elsewhere on the board
DRAM_A14: U2.N7 (A14); also elsewhere on the board
DRAM_BA0: U2.J2 (BA0); also elsewhere on the board
DRAM_BA1: U2.K8 (BA1); also elsewhere on the board
DRAM_BA2: U2.J3 (BA2); also elsewhere on the board
DRAM_CASN: U2.G3 (CAS#); also elsewhere on the board
DRAM_CKE: R14.1, U2.G9 (CKE); also elsewhere on the board
DRAM_CLK_N: R17.2, U2.G7 (CK#); also elsewhere on the board
DRAM_CLK_P: R17.1, U2.F7 (CK); also elsewhere on the board
DRAM_CSN: R15.1, U2.H2 (CS#)
DRAM_DM: U2.B7 (DM/TDQS); also elsewhere on the board
DRAM_DQ0: U2.B3 (DQ0); also elsewhere on the board
DRAM_DQ1: U2.C8 (DQ3); also elsewhere on the board
DRAM_DQ2: U2.C2 (DQ2); also elsewhere on the board
DRAM_DQ3: U2.C7 (DQ1); also elsewhere on the board
DRAM_DQ4: U2.E3 (DQ4); also elsewhere on the board
DRAM_DQ5: U2.E8 (DQ5); also elsewhere on the board
DRAM_DQ6: U2.D2 (DQ6); also elsewhere on the board
DRAM_DQ7: U2.E7 (DQ7); also elsewhere on the board
DRAM_DQS_N: U2.D3 (DQS#); also elsewhere on the board
DRAM_DQS_P: U2.C3 (DQS); also elsewhere on the board
DRAM_ODT: U2.G1 (ODT); also elsewhere on the board
DRAM_RASN: U2.F3 (RAS#); also elsewhere on the board
DRAM_RSTN: R16.1, U2.N2 (RESET#); also elsewhere on the board
DRAM_WEN: U2.H3 (WE#); also elsewhere on the board
GND: C2.2, C3.2, C4.2, C5.2, C6.2, C7.2, C8.2, C9.2, C10.2, C11.2, C12.2, C13.2, C14.2, C15.2, C16.2, C17.2, C18.2, R13.2, R14.2, R15.2, R16.2, U2.A1 (VSS), U2.A8 (VSS), U2.B1 (VSS), U2.B2 (VSSQ), U2.B8 (VSSQ), U2.C9 (VSSQ), U2.D1 (VSSQ), U2.D8 (VSS), U2.D9 (VSSQ), U2.F2 (VSS), U2.F8 (VSS), U2.J1 (VSS), U2.J9 (VSS), U2.L1 (VSS), U2.L9 (VSS), U2.N1 (VSS), U2.N9 (VSS), U3.4 (GND), U4.13 (VSS), U4.36 (VSS); also elsewhere on the board
NAND_ALE: U4.17 (ALE); also elsewhere on the board
NAND_CEN: U4.9 (CEN); also elsewhere on the board
NAND_CLE: U4.16 (CLE); also elsewhere on the board
NAND_IO0: U4.29 (IO0); also elsewhere on the board
NAND_IO1: U4.30 (IO1); also elsewhere on the board
NAND_IO2: U4.31 (IO2); also elsewhere on the board
NAND_IO3: U4.32 (IO3); also elsewhere on the board
NAND_IO4: U4.41 (IO4); also elsewhere on the board
NAND_IO5: U4.42 (IO5); also elsewhere on the board
NAND_IO6: U4.43 (IO6); also elsewhere on the board
NAND_IO7: U4.44 (IO7); also elsewhere on the board
NAND_REN: U4.8 (REN); also elsewhere on the board
NAND_R/BN: U4.7 (R/BN); also elsewhere on the board
NAND_WEN: U4.18 (WEN); also elsewhere on the board
NAND_WPN: U4.19 (WPN); also elsewhere on the board
unnamed: R13.1, U2.H8 (ZQ)
unnamed: R12.1, U3.6 (CLK)
QSPI_CLK: R12.2; also elsewhere on the board
QSPI_CSN: R9.2, U3.1 (~CS); also elsewhere on the board
QSPI_D0: U3.5 (DI(IO0)); also elsewhere on the board
QSPI_D1: U3.2 (DO(IO1)); also elsewhere on the board
QSPI_D2: R10.2, U3.3 (IO2); also elsewhere on the board
QSPI_D3: R11.2, U3.7 (IO3); also elsewhere on the board
VREF_DRAM: C17.1, C18.1, U2.E1 (VREFDQ), U2.J8 (VREFCA); also elsewhere on the board

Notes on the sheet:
QSPI Flash
DDR3L
NAND Flash
